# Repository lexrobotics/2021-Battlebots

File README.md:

# 2021-Battlebots

Q: What am I looking at here?

A: 

📦2021-Battlebots \
 ┣ 📂BattlebotsController             `KiCAD files for the battlebots control board hardware` \
 ┣ 📂Code \
 ┃ ┣ 📂peripheralController           `Arduino code for the ATMEGA328P microcontroller` \
 ┃ ┗ 📂wifiController                 `Arduino code for the ESP8266 microcontroller` \
 ┗ 📂OLDVERSION-BattlebotsController  `KiCAD files for the old version of the control board`

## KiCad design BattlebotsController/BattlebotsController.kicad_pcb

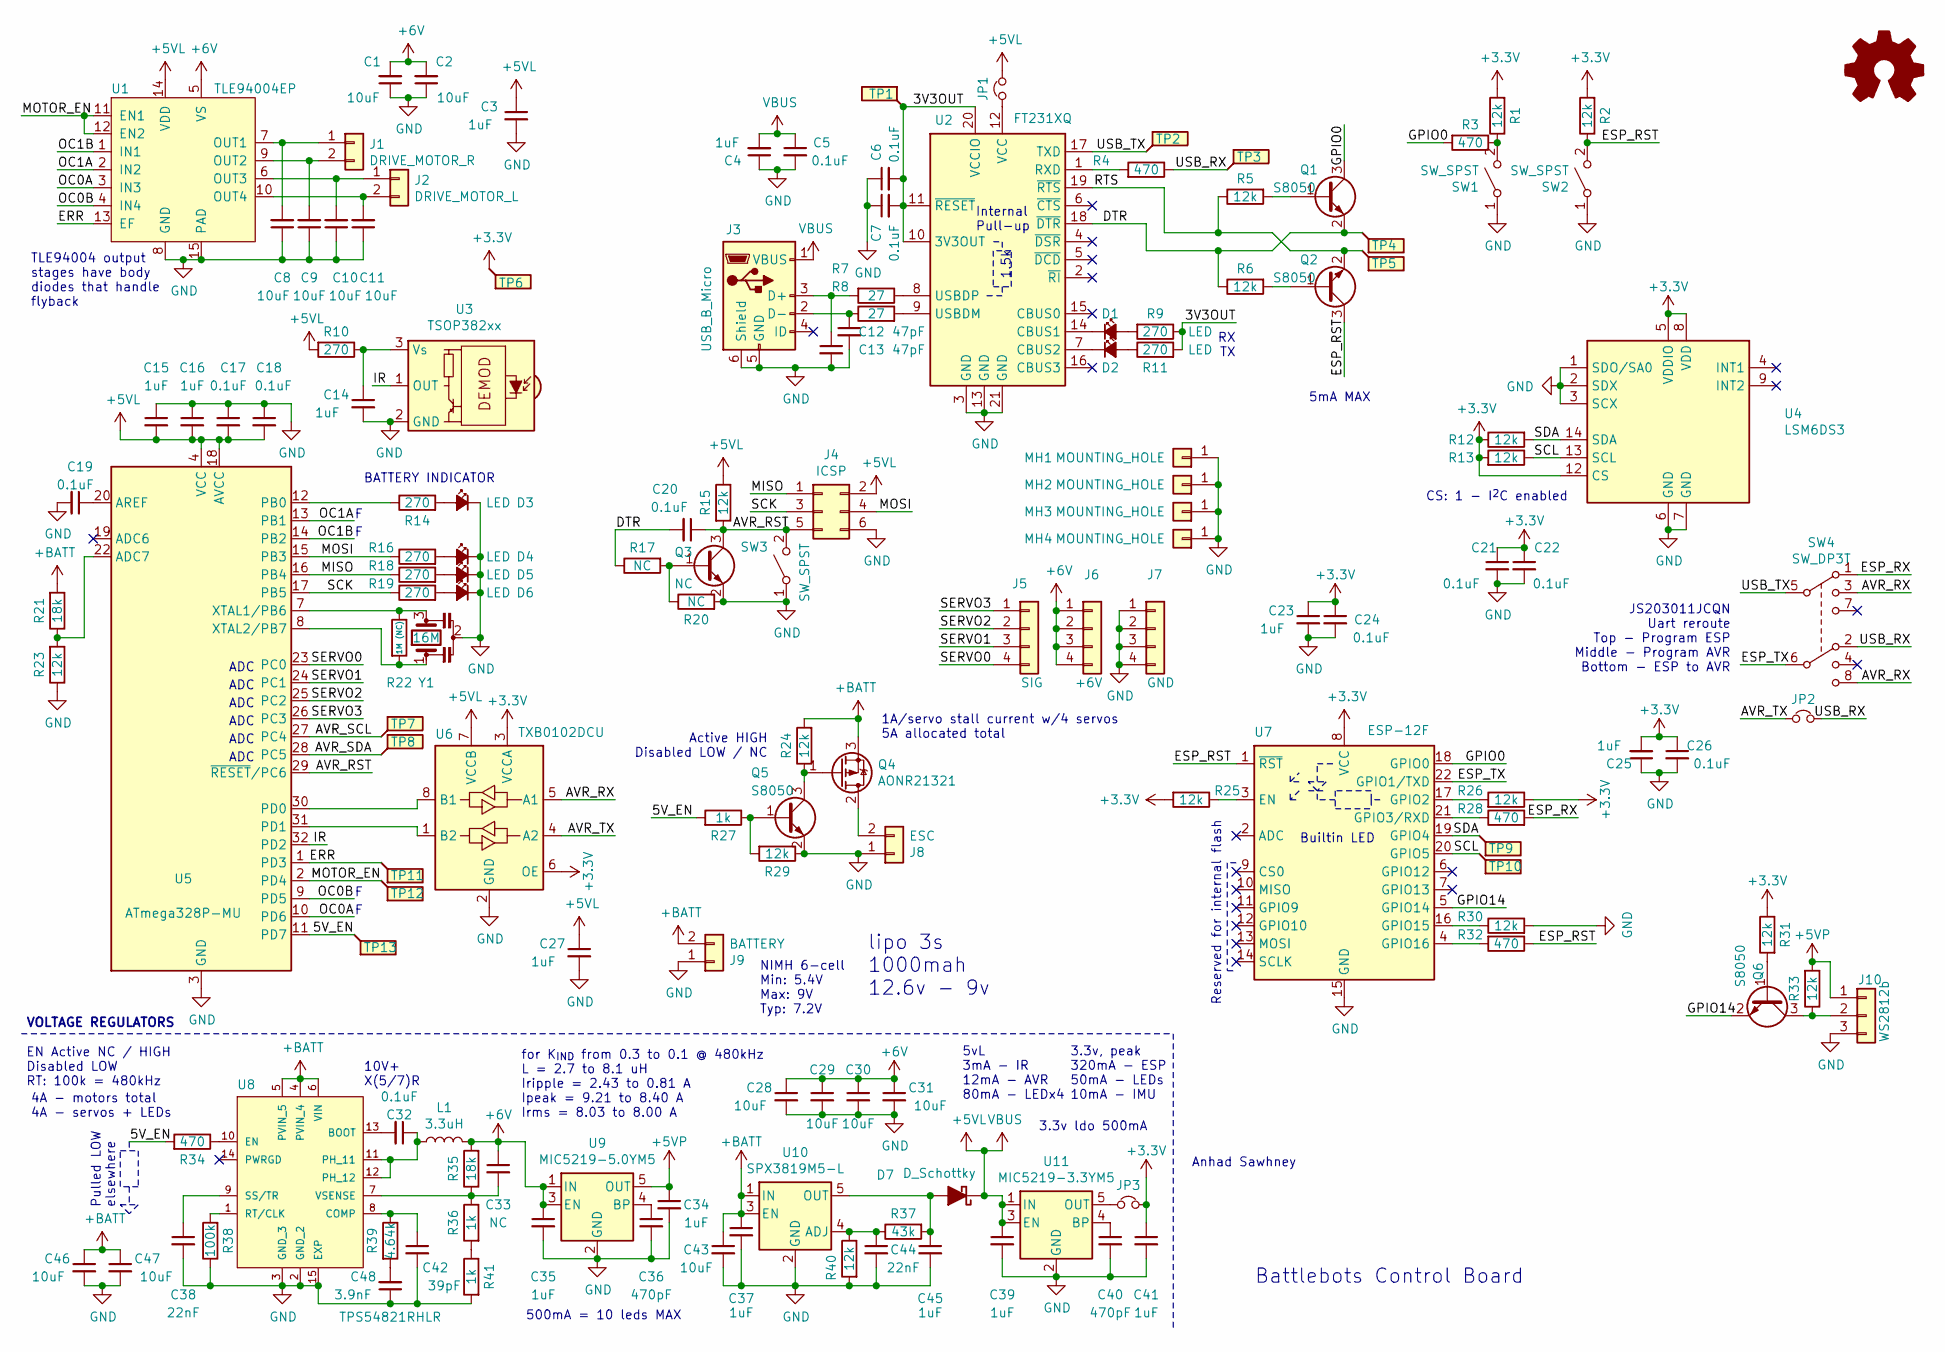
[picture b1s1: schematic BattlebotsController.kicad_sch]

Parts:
C1, C2, C8, C9, C10, C11, C28, C29, C30, C31, C43, C46, C47: 10uF; C_0805_2012Metric
C3, C4, C14, C15, C16, C23, C25, C27, C34, C35, C37, C39, C41, C45: 1uF; C_0402_1005Metric
C5, C6, C7, C17, C18, C19, C20, C21, C22, C24, C26, C32: 0.1uF; C_0402_1005Metric
C12, C13: 47pF; C_0402_1005Metric
C33: NC; C_0402_1005Metric
C36, C40: 470pF; C_0402_1005Metric
C38, C44: 22nF; C_0402_1005Metric
C42: 39pF; C_0402_1005Metric
C48: 3.9nF; C_0402_1005Metric
D1, D2, D3, D4, D5, D6: LED; LED_0603_1608Metric
D7: D_Schottky; D_SOD-323F
J1: DRIVE_MOTOR_R; JST_XH_B2B-XH-A_1x02_P2.50mm_Vertical
J2: DRIVE_MOTOR_L; JST_XH_B2B-XH-A_1x02_P2.50mm_Vertical
J3: USB_B_Micro; USB_Micro-B_Molex-105017-0001
J4: ICSP; PinHeader_2x03_P2.54mm_Vertical
J5: SIG; PinHeader_1x04_P2.54mm_Vertical
J6: +6V; PinHeader_1x04_P2.54mm_Vertical
J7: GND; PinHeader_1x04_P2.54mm_Vertical
J8: ESC; AMASS_XT30U-M_1x02_P5.0mm_Vertical
J9: BATTERY; AMASS_XT30U-M_1x02_P5.0mm_Vertical
J10: WS2812b; PinHeader_1x03_P2.54mm_Vertical
JP1, JP2, JP3: Jumper_NC_Small; SolderJumper-2_P1.3mm_Bridged_RoundedPad1.0x1.5mm
L1: 3.3uH; INDPM5355X310N
MH1, MH2, MH3, MH4: MOUNTING_HOLE; MountingHole_3.2mm_M3_Pad_Via
Q1, Q2, Q5, Q6: S8050; SOT-23
Q3: NC; SOT-23
Q4: AONR21321; TRANS_AONR21321
R1, R2, R5, R6, R12, R13, R15, R23, R24, R25, R26, R29, R30, R31, R33, R40: 12k; R_0402_1005Metric
R3, R4, R28, R32, R34: 470; R_0402_1005Metric
R7, R8: 27; R_0402_1005Metric
R9, R10, R11, R14, R16, R18, R19: 270; R_0402_1005Metric
R17, R20: NC; R_0402_1005Metric
R21, R35: 18k; R_0402_1005Metric
R22: 1M (NC); R_0402_1005Metric
R27, R36, R41: 1k; R_0402_1005Metric
R37: 43k; R_0402_1005Metric
R38: 100k; R_0402_1005Metric
R39: 4.64k; R_0402_1005Metric
SW1, SW2, SW3: SW_SPST; SW_Push_1P1T-SH_NO_CK_KMR2xxG
SW4: SW_DP3T; JS203011JCQN
TP1, TP2, TP3, TP4, TP5, TP6, TP7, TP8, TP9, TP10, TP11, TP12, TP13: TestPoint_Flag; TestPoint_Pad_D1.5mm
U1: TLE94004EP; Infineon_PG-TSDSO-14-22
U2: FT231XQ; QFN-20-1EP_4x4mm_P0.5mm_EP2.5x2.5mm
U3: TSOP382xx; Vishay_MINICAST-3Pin
U4: LSM6DS3; LGA-14_3x2.5mm_P0.5mm_LayoutBorder3x4y
U5: ATmega328P-MU; QFN-32-1EP_5x5mm_P0.5mm_EP3.1x3.1mm
U6: TXB0102DCU; VSSOP-8_2.4x2.1mm_P0.5mm
U7: ESP-12F; ESP-12E
U8: TPS54821RHLR; IC_TPS54821RHLR
U9: MIC5219-5.0YM5; SOT-23-5
U10: SPX3819M5-L; SOT-23-5
U11: MIC5219-3.3YM5; SOT-23-5
Y1: 16M; Resonator_SMD_Murata_CSTxExxV-3Pin_3.0x1.1mm

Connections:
+3V3: C21.1, C22.1, C23.1, C24.1, C25.2, C26.1, C41.1, JP3.2, R1.2, R2.2, R12.1, R13.2, R25.2, R26.1, R31.1, TP6.1, U4.5 (VDDIO), U4.8 (VDD), U4.12 (CS), U6.3 (VCCA), U6.6 (OE), U7.8 (VCC)
+5VL: C3.1, C4.2, C5.1, C15.2, C16.2, C17.2, C18.2, C27.1, C39.1, D7.1 (K), J3.1 (VBUS), J4.2, JP1.2, R10.2, R15.1, U1.14 (VDD), U5.4 (VCC), U5.6 (VCC), U5.18 (AVCC), U6.7 (VCCB), U11.1 (IN), U11.3 (EN)
+5VP: C34.1, J10.1, R33.2, U9.5 (OUT)
+6V: C1.2, C2.2, C28.1, C29.1, C30.1, C31.1, C33.1, C35.1, J6.1, J6.2, J6.3, J6.4, L1.2, R35.2, U1.5 (VS), U9.1 (IN), U9.3 (EN)
+BATT: C37.1, C43.1, C46.1, C47.1, J9.2, Q4.3 (S), R21.2, R24.2, U8.4 (PVIN_4), U8.5 (PVIN_5), U8.6 (VIN), U10.1 (IN), U10.3 (EN)
/3V3OUT: C6.2, C7.2, R9.1, R11.2, TP1.1, U2.10 (3V3OUT), U2.11 (~RESET), U2.20 (VCCIO)
/5V_EN: R27.2, R34.2, TP13.1, U5.11 (PD7)
/AVR_RST: C20.1, J4.5, Q3.3 (C), R15.2, SW3.2 (B), U5.29 (~RESET~/PC6)
/AVR_RX: SW4.3, SW4.8, U6.5 (A1)
/AVR_SCL: TP7.1, U5.27 (PC4)
/AVR_SDA: TP8.1, U5.28 (PC5)
/AVR_TX: JP2.1, U6.4 (A2)
/DTR: C20.2, Q1.2 (E), R6.1, R17.1, TP4.1, U2.18 (~DTR)
/ERR: TP11.1, U1.13 (EF), U5.1 (PD3)
/ESP_RST: Q2.3 (C), R2.1, R32.1, SW2.2 (B), U7.1 (~RST)
/ESP_RX: R28.2, SW4.1
/ESP_TX: SW4.6, U7.22 (GPIO1/TXD)
/GPIO0: Q1.3 (C), R3.2, U7.18 (GPIO0)
/GPIO14: Q6.2 (E), U7.5 (GPIO14)
/IR: U3.1 (OUT), U5.32 (PD2)
/MISO: J4.1, R18.1, U5.16 (PB4)
/MOSI: J4.4, R16.1, U5.15 (PB3)
/MOTOR_EN: TP12.1, U1.11 (EN1), U1.12 (EN2), U5.2 (PD4)
/OC0A: U1.3 (IN3), U5.10 (PD6)
/OC0B: U1.4 (IN4), U5.9 (PD5)
/OC1A: U1.2 (IN2), U5.13 (PB1)
/OC1B: U1.1 (IN1), U5.14 (PB2)
/RTS: Q2.2 (E), R5.1, TP5.1, U2.19 (~RTS)
/SCK: J4.3, R19.1, U5.17 (PB5)
/SCL: R13.1, TP10.1, U4.13 (SCL), U7.20 (GPIO5)
/SDA: R12.2, TP9.1, U4.14 (SDA), U7.19 (GPIO4)
/SERVO0: J5.4, U5.23 (PC0)
/SERVO1: J5.3, U5.24 (PC1)
/SERVO2: J5.2, U5.25 (PC2)
/SERVO3: J5.1, U5.26 (PC3)
/USB_RX: JP2.2, R4.1, SW4.2, TP3.1
/USB_TX: SW4.5, TP2.1, U2.17 (TXD)
GND: C1.1, C2.1, C3.2, C4.1, C5.2, C6.1, C7.1, C8.1, C9.1, C10.1, C11.1, C12.2, C13.2, C14.2, C15.1, C16.1, C17.1, C18.1, C19.2, C21.2, C22.2, C23.2, C24.2, C25.1, C26.2, C27.2, C28.2, C29.2, C30.2, C31.2, C34.2, C35.2, C36.2, C37.2, C38.2, C39.2, C40.2, C41.2, C42.2, C43.2, C44.2, C45.2, C46.2, C47.2, C48.1, D3.1 (K), D4.1 (K), D5.1 (K), D6.1 (K), J3.5 (GND), J3.6 (Shield), J4.6, J7.1, J7.2, J7.3, J7.4, J8.1, J9.1, J10.3, MH1.1, MH2.1, MH3.1, MH4.1, Q3.2 (E), Q5.2 (E), R20.2, R23.1, R29.1, R30.2, R38.1, R40.2, R41.2, SW1.1 (A), SW2.1 (A), SW3.1 (A), U1.8 (GND), U1.15 (PAD), U2.3 (GND), U2.13 (GND), U2.21 (GND), U3.2 (GND), U4.1 (SDO/SA0), U4.2 (SDX), U4.3 (SCX), U4.6 (GND), U4.7 (GND), U5.3 (GND), U5.5 (GND), U5.21 (GND), U5.33 (GND), U6.2 (GND), U7.15 (GND), U8.2 (GND_2), U8.3 (GND_3), U8.15 (EXP), U9.2 (GND), U10.2 (GND), U11.2 (GND), Y1.2
unnamed: C8.2, J1.1, U1.7 (OUT1)
unnamed: C9.2, J1.2, U1.9 (OUT2)
unnamed: C10.2, J2.1, U1.6 (OUT3)
unnamed: C11.2, J2.2, U1.10 (OUT4)
unnamed: C12.1, J3.2 (D-), R8.1
unnamed: C13.1, J3.3 (D+), R7.2
unnamed: C19.1, U5.20 (AREF)
unnamed: C32.1, L1.1, U8.11 (PH_11), U8.12 (PH_12)
unnamed: C32.2, U8.13 (BOOT)
unnamed: C33.2, R35.1, R36.1, U8.7 (VSENSE)
unnamed: C36.1, U9.4 (BP)
unnamed: C38.1, U8.9 (SS/TR)
unnamed: C40.1, U11.4 (BP)
unnamed: C42.1, R39.1, U8.8 (COMP)
unnamed: C44.1, R37.1, R40.1, U10.4 (ADJ)
unnamed: C45.1, D7.2 (A), R37.2, U10.5 (OUT)
unnamed: C48.2, R39.2
unnamed: D1.1 (K), U2.14 (CBUS1)
unnamed: D1.2 (A), R9.2
unnamed: D2.1 (K), U2.7 (CBUS2)
unnamed: D2.2 (A), R11.1
unnamed: D3.2 (A), R14.2
unnamed: D4.2 (A), R16.2
unnamed: D5.2 (A), R18.2
unnamed: D6.2 (A), R19.2
unnamed: J8.2, Q4.2 (D)
unnamed: J10.2, Q6.3 (C), R33.1
unnamed: JP1.1, U2.12 (VCC)
unnamed: JP3.1, U11.5 (OUT)
unnamed: Q1.1 (B), R5.2
unnamed: Q2.1 (B), R6.2
unnamed: Q3.1 (B), R17.2, R20.1
unnamed: Q4.1 (G), Q5.3 (C), R24.1
unnamed: Q5.1 (B), R27.1, R29.2
unnamed: Q6.1 (B), R31.2
unnamed: R1.1, R3.1, SW1.2 (B)
unnamed: R4.2, U2.1 (RXD)
unnamed: R7.1, U2.8 (USBDP)
unnamed: R8.2, U2.9 (USBDM)
unnamed: C14.1, R10.1, U3.3 (Vs)
unnamed: R14.1, U5.12 (PB0)
unnamed: R21.1, R23.2, U5.22 (ADC7)
unnamed: R22.1, U5.7 (XTAL1/PB6), Y1.3
unnamed: R22.2, U5.8 (XTAL2/PB7), Y1.1
unnamed: R25.1, U7.3 (EN)
unnamed: R26.2, U7.17 (GPIO2)
unnamed: R28.1, U7.21 (GPIO3/RXD)
unnamed: R30.1, U7.16 (GPIO15)
unnamed: R32.2, U7.4 (GPIO16)
unnamed: R34.1, U8.10 (EN)
unnamed: R36.2, R41.1
unnamed: R38.2, U8.1 (RT/CLK)
unnamed: U5.30 (PD0), U6.8 (B1)
unnamed: U5.31 (PD1), U6.1 (B2)

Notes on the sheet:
VOLTAGE REGULATORS
EN Active NC / HIGH Disabled LOW RT: 100k = 480kHz
TLE94004 output stages have body diodes that handle flyback
4A - motors total 4A - servos + LEDs
Pulled LOW elsewhere
ADC
BATTERY INDICATOR
10V+ X(5/7)R
for K_{IND} from 0.3 to 0.1 @ 480kHz L = 2.7 to 8.1 uH Iripple = 2.43 to 0.81 A Ipeak = 9.21 to 8.40 A Irms = 8.03 to 8.00 A
500mA = 10 leds MAX
NIMH 6-cell Min: 5.4V Max: 9V Typ: 7.2V
Active HIGH Disabled LOW / NC
lipo 3s 1000mah 12.6v - 9v
1A/servo stall current w/4 servos 5A allocated total
5vL 3mA - IR 12mA - AVR 80mA - LEDx4
Internal Pull-up
1.5k
3.3v ldo 500mA
3.3v, peak 320mA - ESP 50mA - LEDs 10mA - IMU
Anhad Sawhney
RX TX
Reserved for internal flash
Battlebots Control Board
Builtin LED
5mA MAX
CS: 1 - I^{2}C enabled
JS203011JCQN Uart reroute Top - Program ESP Middle - Program AVR Bottom - ESP to AVR

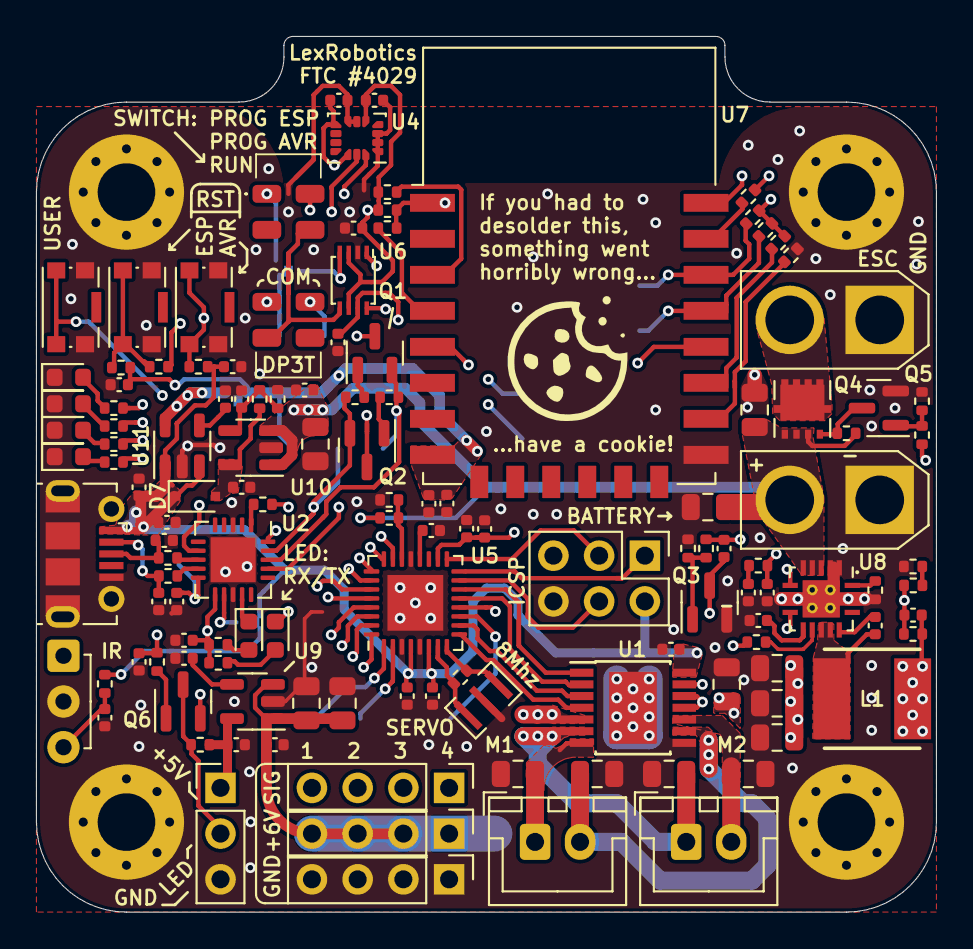
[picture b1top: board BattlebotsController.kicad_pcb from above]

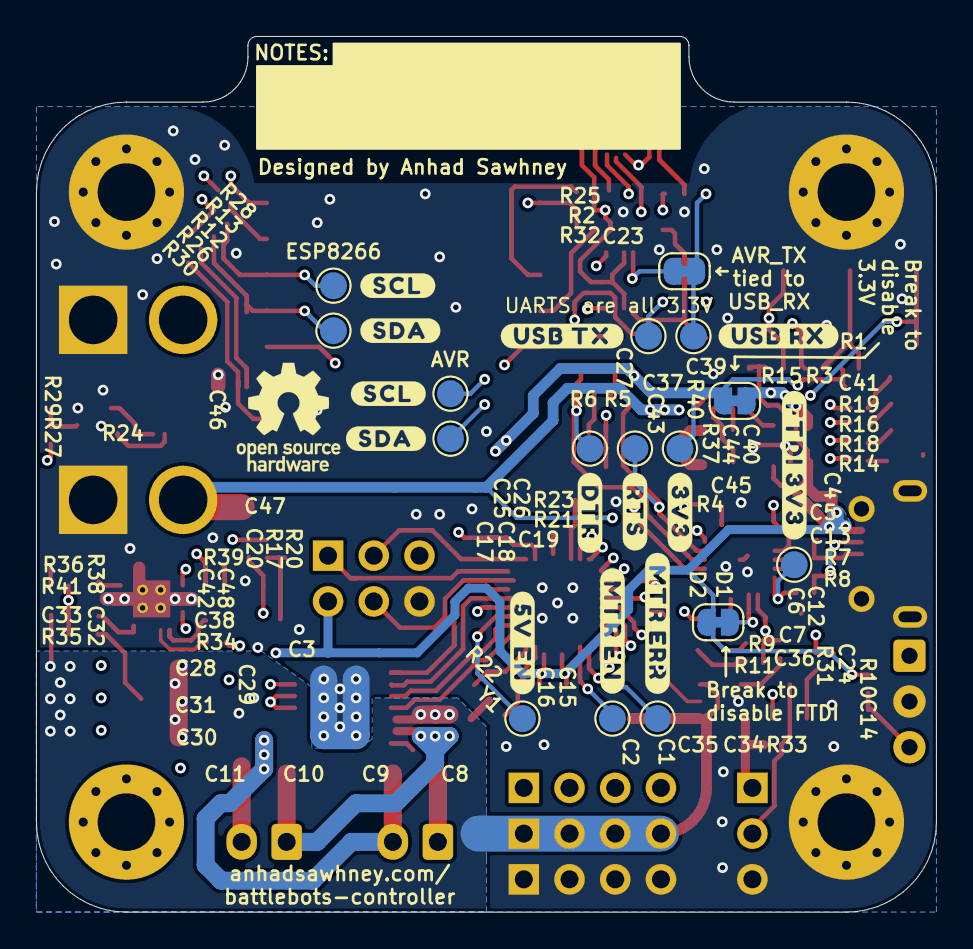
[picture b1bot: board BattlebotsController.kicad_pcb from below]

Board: 4 copper layers, 50.0 x 48.6 mm, 149 parts (16 on the bottom side), 92 nets.

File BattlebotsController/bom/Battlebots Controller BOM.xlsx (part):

| Source: | C:\Users\Anhad\Documents\Kicad\BattlebotsController\BattlebotsController.kicad_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
 | Date: |  | 44290.992615740739
 | Tool: | Eeschema (5.99.0-10089-gf88d39b4f0)
 | Generator: | C:\Program Files\KiCad\bin\scripting\plugins/bom_csv_grouped_by_value_with_fp.py
 | Component Count: | 149 |  |  |  |  |  |  |  | TOTAL: | 30.909999999999989
Item # | *Designator | *Qty | *Mfg Part # | Description / Value | Manufacturer | *Package/Footprint | NOTES | Digikey Part Number | Possible to substitute? | Price (1x) | Price Estimate
1 | C1, C2, C8, C9, C10, C11, C28, C29, C30, C31, C43, C46, C47, | 13 | CL21A106KOQNNNE | 10uf | Samsung Electromechanics | Capacitor_SMD:C_0805_2012Metric | Capacitors must all be >=10V | 1276-1096-1-ND | YES | 0.11 | 1.43
2 | C3, C4, C14, C15, C16, C23, C25, C27, C34, C35, C37, C39, C41, C45, | 14 | GRM155R61C105MA12D | 1uF | Murata Electronics | Capacitor_SMD:C_0402_1005Metric |  | 490-14599-1-ND | YES | 0.1 | 1.4000000000000001
3 | C5, C6, C7, C17, C18, C19, C20, C21, C22, C24, C26, C32, | 12 | EMF105B7104KVHF | 0.1uF | Taiyo Yuden | Capacitor_SMD:C_0402_1005Metric |  | 587-6563-1-ND | YES | 0.1 | 1.2000000000000002
4 | C12, C13, | 2 | CC0402GRNPO9BN470 | 47pF | Yageo | Capacitor_SMD:C_0402_1005Metric |  | 311-3741-1-ND | YES | 0.1 | 0.2
5 | C33, | 1 |  | NC |  | Capacitor_SMD:C_0402_1005Metric | DO NOT POPULATE |  |  |  | 0
6 | C36, C40, | 2 | CC0402JRX7R9BB471 | 470pF | Yageo | Capacitor_SMD:C_0402_1005Metric |  | 311-1679-1-ND | YES | 0.1 | 0.2
7 | C38, C44, | 2 | GRM155R71E223JA61D | 22nF | Murata Electronics | Capacitor_SMD:C_0402_1005Metric |  | 490-10699-1-ND | YES | 0.1 | 0.2
8 | C42, | 1 | CL05C390JB51PNC | 39pF | Samsung Electromechanics | Capacitor_SMD:C_0402_1005Metric |  | 1276-6863-1-ND | YES | 0.1 | 0.1
9 | C48, | 1 | CC0402JRX7R9BB392 | 3.9nF | Yageo | Capacitor_SMD:C_0402_1005Metric |  | 311-3771-1-ND | YES | 0.1 | 0.1
10 | D1, D2, D3, D4, D5, D6, | 6 | 150060VS75000 | LED 20mA, 2V | Würth Elektronik | LED_SMD:LED_0603_1608Metric | Green | 732-4980-1-ND | YES | 0.14000000000000001 | 0.84000000000000008
11 | D7, | 1 | PMEG4005EJ,115 | Schottky Diode | Nexperia USA Inc. | Diode_SMD:D_SOD-323F | < 0.5V voltage drop | 1727-3877-1-ND | YES | 0.31 | 0.31
12 | J3, | 1 | 1050170001 | USB_B_Micro | Molex | Connector_USB:USB_Micro-B_Molex-105017-0001 |  | WM1399CT-ND | NO | 0.83 | 0.83
13 | L1, | 1 | SRP5030CA-3R3M | 3.3uH | Bourns Incorporated | SRP5030CA:INDPM5355X310N | Shielded | SRP5030CA-3R3MCT-ND | NO | 1.65 | 1.65
14 | Q1, Q2, Q5, Q6, | 4 | MMSS8050-H-TP | S8050 | Micro Commercial Co. | Package_TO_SOT_SMD:SOT-23 | 0.7A Ic, 20V Vce, Low Voltage High Current NPN Transistor, TO-92 | MMSS8050-H-TPMSCT-ND | YES | 0.18 | 0.72
15 | Q3, | 1 | NC (S8050) | Q_NPN_BEC |  | Package_TO_SOT_SMD:SOT-23 | DO NOT POPULATE |  | YES
16 | Q4, | 1 | AONR21307 | P-MOSFET transistor, gate/drain/source | Alpha & Omega Semiconductor | AONR21307:TRANS_AONR21321 |  | 785-1796-1-ND | YES | 0.56000000000000005 | 0.56000000000000005
17 | R1, R2, R5, R6, R12, R13, R15, R23, R24, R25, R26, R29, R30, R31, R33, R40, | 16 | RC0402FR-0712KL | 12k | Yageo | Resistor_SMD:R_0402_1005Metric |  | 311-12.0KLRCT-ND | YES | 0.1 | 1.6
18 | R3, R4, R28, R32, R34, | 5 | CRCW0402470RFKEDC | 470 | Vishay Dale | Resistor_SMD:R_0402_1005Metric |  | 541-4072-1-ND | YES | 0.1 | 0.5
19 | R7, R8, | 2 | AC0402FR-0727RL | 27 | Yageo | Resistor_SMD:R_0402_1005Metric |  | YAG5278CT-ND | YES
20 | R9, R10, R11, R14, R16, R18, R19, | 7 | RC0402FR-07270RL | 270 | Yageo | Resistor_SMD:R_0402_1005Metric |  | 311-270LRCT-ND | YES | 0.1 | 0.70000000000000007
21 | R17, R20, R22, | 3 |  | NC |  | Resistor_SMD:R_0402_1005Metric | DO NOT POPULATE
22 | R21, R35, | 2 | CRCW040218K0FKED | 18k | Vishay Dale | Resistor_SMD:R_0402_1005Metric |  | 541-18.0KLCT-ND | YES | 0.1 | 0.2
23 | R27, R36, R41, | 3 | CRCW04021K00FKEDC | 1k | Vishay Dale | Resistor_SMD:R_0402_1005Metric |  | 541-3961-1-ND | YES | 0.1 | 0.30000000000000004
24 | R37, | 1 | RC0402FR-0743KL | 43k | Yageo | Resistor_SMD:R_0402_1005Metric |  | 311-43.0KLRCT-ND | YES | 0.1 | 0.1
25 | R38, | 1 | RC0402DR-07100KL | 100k | Yageo | Resistor_SMD:R_0402_1005Metric |  | 13-RC0402DR-07100KLCT-ND | YES | 0.1 | 0.1
26 | R39, | 1 | CRCW04024K64FKED | 4.64k | Vishay Dale | Resistor_SMD:R_0402_1005Metric |  | 541-4.64KLCT-ND | YES | 0.1 | 0.1
27 | SW1, SW2, SW3, | 3 | KMR221GLFS | SPST BUTTON | C&K | Button_Switch_SMD:SW_Push_1P1T-SH_NO_CK_KMR2xxG |  | 401-1427-1-ND | NO | 0.48 | 1.44
28 | SW4, | 1 | JS203011JCQN | DP3T SLIDE | C&K | BattlebotsController:JS203011JCQN | Switch, three position, double pole triple throw, 3 position switch, SP3T | CKN10725CT-ND | NO | 0.65 | 0.65
29 | U1, | 1 | TLE94004EP | Motor Driver | Infineon | Package_SO:Infineon_PG-TSDSO-14-22 |  | TLE94004EPXUMA1CT-ND | NO | 2.0699999999999998 | 2.0699999999999998
30 | U2, | 1 | FT231XQ | USB - UART | FTDI, Future Technology Devices International Ltd | Package_DFN_QFN:QFN-20-1EP_4x4mm_P0.5mm_EP2.5x2.5mm | Full Speed USB to Full Handshake UART, QFN-20 | 768-1155-ND | NO | 2.2200000000000002 | 2.2200000000000002
31 | U4, | 1 | LSM6DSM | LSM6DSx | STMicroelectronics | Package_LGA:LGA-14_3x2.5mm_P0.5mm_LayoutBorder3x4y | DO NOT POPULATE | 497-16696-1-ND | YES | 2.92 | 2.92
32 | U5, | 1 | ATmega328P-MU | 20MHz, 32kB Flash, 2kB SRAM, 1kB EEPROM, QFN-32 | Microchip Technology | Package_DFN_QFN:QFN-32-1EP_5x5mm_P0.5mm_EP3.1x3.1mm |  | ATMEGA328P-MU-ND | NO | 2.0099999999999998 | 2.0099999999999998
33 | U6, | 1 | TXB0102DCU | Level Shifter | Texas Instruments | Package_SO:VSSOP-8_2.4x2.1mm_P0.5mm | 2-Bit Bidirectional Voltage-Level Translator in VSSOP Package With Auto Directi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 | 296-22862-1-ND | NO | 0.76 | 0.76
34 | U7, | 1 | ESP-12F | ESP8266 Module | Ai-Thinker | RF_Module:ESP-12E/F | 802.11 b/g/n Wi-Fi Module |  | NO* |  | 0
35 | U8, | 1 | TPS54821RHLR | 8A Buck Converter | Texas Instruments | TPS54821:IC_TPS54821RHLR |  | 296-29744-1-ND | NO | 2.92 | 2.92
36 | U9, | 1 | MIC5219-5.0YM5 | FIXED 5V!!!! | Microchip Technology | Package_TO_SOT_SMD:SOT-23-5 | 500mA low dropout linear regulator, fixed 5.0V output, SOT-23-5 | 576-2770-1-ND | YES | 0.89 | 0.89
37 | U10, | 1 | SPX3819M5-L | ADJUSTABLE!!!! | MaxLinear Incorporated | Package_TO_SOT_SMD:SOT-23-5 | 500mA Low drop-out regulator, Adjustable, SOT-23-5 | 1016-1873-1-ND | NO | 0.49 | 0.49
38 | U11, | 1 | MIC5219-3.3YM5 | FIXED 3.3V!!!! | Microchip Technology | Package_TO_SOT_SMD:SOT-23-5 | 500mA low dropout linear regulator, fixed 3.3V output, SOT-23-5 | 576-1281-1-ND | YES | 0.93 | 0.93
39 | Y1, | 1 | CSTNE16M0V530000R0 | 16M resonator | Murata Electronics | Crystal:Resonator_SMD_muRata_CSTxExxV-3Pin_3.0x1.1mm | Three pin ceramic resonator | 490-17948-1-ND | YES | 0.27 | 0.27
40
41
42
 | NOT POPULATED / THRU HOLE | PCBWAY - IGNORE
Item # | *Designator | *Qty | *Mfg Part # | Description / Value | Manufacturer | *Package/Footprint | NOTES | Digikey Part Number | Possible to substitute with another equivalent part? | Price (1x) | Unit Price
43 | TP1, TP2, TP3, TP4, TP5, TP6, TP7, TP8, TP9, TP10, TP11, TP12, TP13, | 13 |  | TestPoint_Flag | TestPoint_Flag | TestPoint:TestPoint_Pad_D1.5mm | DO NOT POPULATE
44 | JP1, JP2, JP3, | 3 |  | Jumper_NC_Small | Jumper_NC_Small | Jumper:SolderJumper-2_P1.3mm_Bridged_RoundedPad1.0x1.5mm | DO NOT POPULATE
45 | MH1, MH2, MH3, MH4, | 4 |  | MOUNTING_HOLE | Conn_01x01 | MountingHole:MountingHole_3.2mm_M3_Pad_Via | DO NOT POPULATE
46 | J4, | 1 |  | ICSP | Conn_02x03_Odd_Even | Connector_PinHeader_2.54mm:PinHeader_2x03_P2.54mm_Vertical | DO NOT POPULATE
47 | J5, | 1 |  | SIG | Conn_01x04 | Connector_PinHeader_2.54mm:PinHeader_1x04_P2.54mm_Vertical | DO NOT POPULATE
48 | J6, | 1 |  | +6V | Conn_01x04 | Connector_PinHeader_2.54mm:PinHeader_1x04_P2.54mm_Vertical | DO NOT POPULATE
49 | J7, | 1 |  | GND | Conn_01x04 | Connector_PinHeader_2.54mm:PinHeader_1x04_P2.54mm_Vertical | DO NOT POPULATE
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
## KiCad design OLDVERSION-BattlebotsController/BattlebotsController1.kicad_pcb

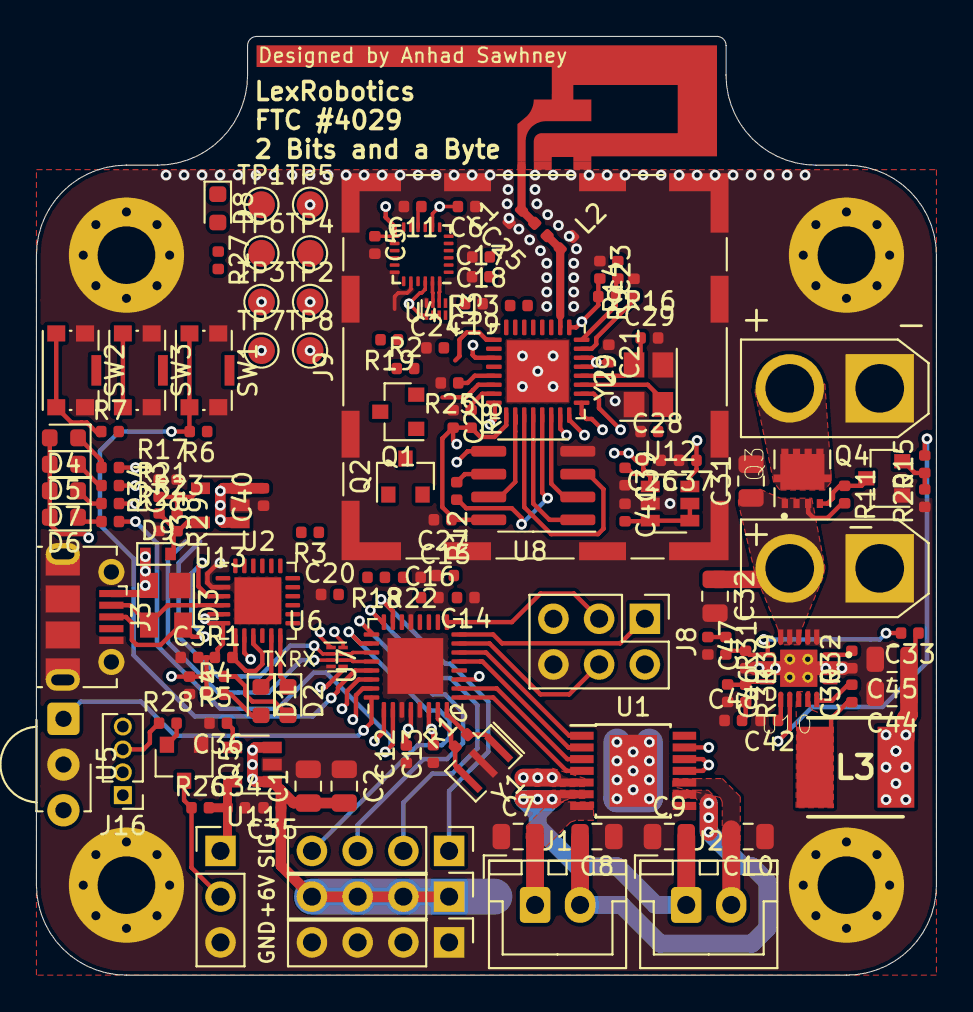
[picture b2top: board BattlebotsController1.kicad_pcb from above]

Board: 4 copper layers, 50.0 x 52.1 mm, 142 parts (0 on the bottom side), 96 nets.

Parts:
ANT1: Inverted F; SWRU120B
C1, C2: 10uf; C_0805_2012Metric
C3, C26, C37, C39: 1uF; C_0402_1005Metric
C4, C5, C6, C11, C17, C18, C19, C20, C27: 0.1uF; C_0402_1005Metric
C7, C8, C9, C10, C31, C32, C44, C45: 10uF; C_0805_2012Metric
C12, C13, C21, C22, C41: 1uf; C_0402_1005Metric
C14, C15, C16, C23, C24: 0.1uf; C_0402_1005Metric
C25: 5.6pf; C_0402_1005Metric
C28, C29: NC; C_0402_1005Metric
C30, C42: 10uF; C_0402_1005Metric
C33, C35, C47: 330pf; C_0402_1005Metric
C34, C38, C40: 2.2uf; C_0402_1005Metric
C36, C43: 470pf; C_0402_1005Metric
C46: 14pf; C_0402_1005Metric
C48: 33nf; C_0402_1005Metric
D1: RXLED; LED_0603_1608Metric
D2: TXLED; LED_0603_1608Metric
D3: SP0503BAHT; SOT-143
D4, D5, D6, D7: LED; LED_0603_1608Metric
D8: ESP_LED; LED_0603_1608Metric
D9: MSK4005; D_SOD-523
J1: DRIVE_MOTOR_R; JST_XH_B2B-XH-A_1x02_P2.50mm_Vertical
J2: DRIVE_MOTOR_L; JST_XH_B2B-XH-A_1x02_P2.50mm_Vertical
J3: USB_B_Micro; USB_Micro-B_Molex-105017-0001
J4, J5, J6, J7: MOUNTING_HOLE; MountingHole_3.2mm_M3_Pad_Via
J8: ICSP; PinHeader_2x03_P2.54mm_Vertical
J9: RF_SHIELD; Wuerth_36103205_20x20mm
J10: SIG; PinHeader_1x04_P2.54mm_Vertical
J11: +6V; PinHeader_1x04_P2.54mm_Vertical
J12: GND; PinHeader_1x04_P2.54mm_Vertical
J13: ESC; AMASS_XT30U-M_1x02_P5.0mm_Vertical
J14: BATTERY; AMASS_XT30U-M_1x02_P5.0mm_Vertical
J15: WS2812b; PinHeader_1x03_P2.54mm_Vertical
J16: LED_DMA; PinHeader_1x04_P1.27mm_Vertical
L1, L2: NC; L_0402_1005Metric
L3: 3.3uH; INDPM5355X310N
Q1, Q2, Q4, Q5: S8050; SOT-23
Q3: Q_PMOS_GDS; TRANS_AONR21321
R1, R15: 1k; R_0402_1005Metric
R2, R3, R6, R7, R8, R11, R13, R14, R16, R20, R25, R28: 12k; R_0402_1005Metric
R4, R5, R17, R21, R23, R24, R27: 270; R_0402_1005Metric
R9: 470; R_0402_1005Metric
R10: 1M; R_0402_1005Metric
R12: 200; R_0402_1005Metric
R18: 56k; R_0402_1005Metric
R19: 499; R_0402_1005Metric
R22: 36k; R_0402_1005Metric
R26: 10k; R_0402_1005Metric
R29: 150k; R_0402_1005Metric
R30, R31, R33: 365k; R_0402_1005Metric
R32: 100k; R_0402_1005Metric
R34: 43k; R_0402_1005Metric
SW1, SW2, SW3: SW_SPST; SW_Push_1P1T-SH_NO_CK_KMR2xxG
TP1, TP2, TP3, TP4, TP5, TP6, TP7, TP8: TestPoint_Flag; TestPoint_Pad_D1.5mm
U1: TLE94004EP; Infineon_PG-TSDSO-14-22
U2: CP2102N-A01-GQFN24; QFN-24-1EP_4x4mm_P0.5mm_EP2.6x2.6mm
U3, U6: TXS0102DQE; X2SON-8_1.4x1mm_P0.35mm
U4: ICM-20948; InvenSense_QFN-24_3x3mm_P0.4mm
U5: TSOP382xx; Vishay_MINICAST-3Pin
U7: ATmega328P-MU; QFN-32-1EP_5x5mm_P0.5mm_EP3.1x3.1mm
U8: AT25SF321B-SSHB-T; SOIC-8_3.9x4.9mm_P1.27mm
U9: ESP8266EX; QFN-32-1EP_5x5mm_P0.5mm_EP3.45x3.45mm
U10: TPS54821RHLR; IC_TPS54821RHLR
U11: MIC5219-5.0YM5; SOT-23-5
U12: AP7312-1833W6-7; SOT-23-6
U13: SPX3819M5-L; SOT-23-5
Y1: 16M; Resonator_SMD_muRata_CSTxExxV-3Pin_3.0x1.1mm
Y2: 26M; Crystal_SMD_SeikoEpson_TSX3225-4Pin_3.2x2.5mm

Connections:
+1V8: C5.1, C6.2, C17.2, C18.1, C37.1, TP4.1, U3.1, U3.5, U4.8, U4.13, U4.22, U12.6
+3V3: C3.2, C4.1, C19.2, C21.2, C22.2, C23.2, C24.2, C26.2, C27.1, C39.1, R1.1, R4.1, R5.2, R7.2, R8.2, R13.1, R16.1, R27.2, TP5.1, U2.5, U2.6, U3.8, U6.1, U6.5, U8.8, U9.1, U9.3, U9.4, U9.5, U9.11, U9.17, U9.29, U9.30, U12.1
+5VL: C12.2, C13.2, C14.2, C15.2, C20.2, C41.2, D3.2, D9.1, J3.1, J8.2, R6.1, TP1.1, U1.14, U2.8, U5.3, U6.8, U7.4, U7.6, U7.18, U12.3, U12.4, U12.5
+5VP: C34.1, D4.2, D5.2, D6.2, D7.2, J15.1, R26.2, U11.5
+6V: C1.1, C2.2, C33.1, C35.1, C44.1, C45.1, J11.1, J11.2, J11.3, J11.4, L3.2, U1.5, U11.1, U11.3
+BATT: C31.1, C32.1, C40.2, J14.2, Q3.3, R11.2, R18.2, U10.4, U10.5, U10.6, U13.1, U13.3
/5V_EN: R15.2, TP6.1, U7.31, U10.10
/AVR_RST: J8.5, R6.2, SW1.2, U7.29
/AVR_SCL: TP8.1, U6.6, U7.28
/AVR_SDA: TP7.1, U6.7, U7.27
/D0: U8.2, U9.22
/D1: U8.5, U9.23
/D2: U8.7, U9.18
/D3: U8.3, U9.19
/ERR: U1.13, U7.1
/ESP_RST: Q2.3, R9.1, R16.2, U9.32
/FTDI_RX_ESP_TX: R19.2, TP2.1, U2.20
/FTDI_TX_ESP_RX: J16.1, TP3.1, U2.21
/GPIO0: Q1.3, R8.1, SW3.2, U9.15
/GPIO5: J16.4, U9.24
/GPIO16: R7.1, R9.2, SW2.2, U9.8
/IR: U5.1, U7.32
/MISO: J8.1, R17.1, U7.16
/MOSI: J8.4, R21.1, U7.15
/MOTOR_EN: U1.11, U1.12, U7.30
/OC0A: U1.3, U7.10
/OC0B: U1.4, U7.9
/OC1A: U1.2, U7.13
/OC1B: U1.1, U7.14
/SCK: J8.3, U7.17
/SCL: U3.6, U6.3, U9.9
/SDA: U3.7, U6.2, U9.14
/SERVO0: J10.1, U7.23
/SERVO1: J10.2, U7.24
/SERVO2: J10.3, U7.25
/SERVO3: J10.4, U7.26
/U0RXD: J16.2, U9.25
GND: ANT1.2, C1.2, C2.1, C3.1, C4.2, C5.2, C6.1, C7.1, C8.1, C9.1, C10.1, C11.2, C12.1, C13.1, C14.1, C15.1, C16.2, C17.1, C18.2, C19.1, C20.1, C21.1, C22.1, C23.1, C24.1, C26.1, C27.2, C28.1, C29.1, C31.2, C32.2, C34.2, C35.2, C36.2, C37.2, C38.2, C39.2, C40.1, C41.1, C42.2, C43.2, C44.2, C45.2, C46.2, C47.2, C48.1, D3.1, J3.5, J3.6, J4.1, J5.1, J6.1, J7.1, J8.6, J9.1, J12.1, J12.2, J12.3, J12.4, J13.1, J14.1, J15.3, L1.2, L2.2, Q4.1, Q5.1, R14.2, R20.1, R22.1, R25.2, R30.2, R32.1, R34.2, SW1.1, SW2.1, SW3.1, U1.8, U1.15, U2.2, U2.25, U3.4, U4.9, U4.18, U4.20, U5.2, U6.4, U7.3, U7.5, U7.21, U7.33, U8.4, U9.33, U10.2, U10.3, U10.15, U10.16, U10.17, U10.18, U10.19, U11.2, U12.2, U13.2, Y1.2, Y2.2, Y2.4
unnamed: ANT1.1, C25.2, L1.1
unnamed: C7.2, J1.1, U1.7
unnamed: C8.2, J1.2, U1.9
unnamed: C9.2, J2.1, U1.6
unnamed: C10.2, J2.2, U1.10
unnamed: C11.1, U4.10
unnamed: C16.1, U7.20
unnamed: C25.1, L2.1, U9.2
unnamed: C28.2, U9.27, Y2.1
unnamed: C29.2, U9.28, Y2.3
unnamed: C30.1, L3.1, U10.11, U10.12
unnamed: C30.2, U10.13
unnamed: C33.2, R30.1, R31.2, U10.7
unnamed: C36.1, U11.4
unnamed: C38.1, D9.2, R29.2, U13.5
unnamed: C42.1, U10.9
unnamed: C43.1, R29.1, R34.1, U13.4
unnamed: C46.1, R33.1, U10.8
unnamed: C47.1, R31.1
unnamed: C48.2, R33.2
unnamed: D1.1, U2.11
unnamed: D1.2, R4.2
unnamed: D2.1, U2.12
unnamed: D2.2, R5.1
unnamed: D3.3, J3.2, U2.4
unnamed: D3.4, J3.3, U2.3
unnamed: D4.1, R17.2
unnamed: D5.1, R21.2
unnamed: D6.1, R23.2
unnamed: D7.1, R24.2
unnamed: D8.1, U9.16
unnamed: D8.2, R27.1
unnamed: J13.2, Q3.2
unnamed: J15.2, Q5.3, R26.1
unnamed: J16.3, R28.1
unnamed: Q1.1, R3.1, U2.23
unnamed: Q1.2, R2.2
unnamed: Q2.1, R2.1, U2.19
unnamed: Q2.2, R3.2
unnamed: Q3.1, Q4.3, R11.1
unnamed: Q4.2, R15.1, R20.2
unnamed: Q5.2, R28.2
unnamed: R1.2, U2.7, U2.9
unnamed: R10.1, U7.7, Y1.3
unnamed: R10.2, U7.8, Y1.1
unnamed: R12.1, U8.6
unnamed: R12.2, U9.21
unnamed: R13.2, U9.7
unnamed: R14.1, U9.31
unnamed: R18.1, R22.2, U7.22
unnamed: R19.1, U9.26
unnamed: R23.1, U7.2
unnamed: R24.1, U7.11
unnamed: R25.1, U9.13
unnamed: R32.2, U10.1
unnamed: U3.2, U4.24
unnamed: U3.3, U4.23
unnamed: U8.1, U9.20

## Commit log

2021-04-29 UPLOAD ALL THE THINGS
2021-04-30 prototype code
2021-05-25 update stuff
